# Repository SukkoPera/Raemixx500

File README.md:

# Rämixx500
Rämixx500 is an Open Hardware remake of the Commodore Amiga 500+ mainboard, revision 8A.1.

## Summary
Many Amiga 500+ computers are suffering an early death because of the built-in barrel battery that powers their internal real-time clocks. Such batteries have long exceeded their planned lives and in many cases have started to leak alkaline liquids over the mainboard, corroding copper traces and destroying components.

This damage can sometimes be repaired trivially, but many times it requires a lot of time and effort. Sometimes it adds up to other damage occurred over time and so it would just be better to have a new board built with new components to move the few critical chips over. Amiga mainboards haven't been produced for the last 30 years, but they are relatively simple by today's standards, thus an amateur project to make new ones was started.

There are other projects with the same goal out there, but none of them is Open Source and none of them comes with both schematics and board. This is a big advantage, since anyone can modify the board and make new improved versions, as long as they release their modifications it with the same license. I have come up with [some ideas for improvements](https://github.com/SukkoPera/Raemixx500/issues/14), feel free to help :).

The first version of the board was released in April 2020 as untested, in the hope that someone from the Amiga "Community" would jump in and help with the testing. Well, that took quite some time but in the end someone finally understood that Open Hardware is about trying to do your part rather than coming up with [heaps of useless talking and moaning](https://news.ycombinator.com/item?id=22887349) or [blatant stealing](https://retrotechlyfe.com/home/ols/products/commodore-amiga-500-computer-motherboard-logic-board-premium-gold-immersed-traces-stellar-signal-integrity) and allowed this project to reach the next milestone. So despite knowing he could be jumping into the void, fellow Italian living in Japan Edoardo Auteri put confidence, money, time and effort into assembling a board and testing it thoroughly. While he was at it, he came up with some interesting ideas which ultimately encouraged me to make Version 2, which **fully passed all tests**. You can read more about the development and testing of the board on [the official development blog](https://hackaday.io/project/180442-rmixx500-amiga-500-mainboard).

## Differences from Original
The initial objective was to come up with a new mainboard as similar to the original one as possible, while including minor modifications that would improve its usability. This mainboard was designed with *reasonable* - not *maniacal* - accuracy to the original design. Most care was taken in the positioning of components that ought to be in a certain position (i.e.: screw holes and I/O connectors), to ensure drop-in replaceability. Other components and tracks are "more or less" there, but as the board was wholly laid out from scratch by hand, don't expect sub-millimeter accuracy.

Some modifications were soon added in, in the hope that they would be useful. Let's make it clear straight from the beginning that **most of these improvements and modifications are completely optional and actually disabled by default**. This means that you can just ignore them and everything will work as it did on the original A500+ board. If you want to take advantage of them instead, you will need to do some work.

### Modifications introduced in V2
* **Buffered Video Synchronization Signals**: This will make the VSYNC and HSYNC signals going out from the DB23 connector somewhat "stronger", which should improve video quality and also allow using fully passive (i.e.: just wires) RGB to VGA cables (but please note that the signal will still be 15 kHz so a scandoubler will still be required with most VGA monitors). To enable this, cut both the JP99H/V jumpers, solder a 74HCT14 SOIC chip at U94 (yes, it's surface-mount, but the available space was limited) and a 100-330nF ceramic capacitor at C94. Note that if you want to get back to unbuffered (why???) you will **both** need to unsolder U94 and close the jumpers again, otherwise you will definitely damage your Denise and/or buffer. One small caveat: you'd better decide what to do with this mod before you solder the nearby components, as space around U94 is really tight and (un)soldering it with the other components in place is not a task for the faint-hearted.

* **ESD Protection for the Joystick Ports**: While connecting controllers blindly is **still not recommended**, you can add some diodes that *should* hopefully avoid damage to the internal chips whenever you do so. These won't hurt in any case, so why not? Just solder some AT1042 chips at U90-U93. Yes, they are small but you can make it.

* **Hard Disk LED**: If you use an internal expansion board that provides an IDE connector, you will feel the need for a LED flashing whenever the disk is accessed. If you connect a wire from pin 39 of your CF adapter to the new *HDACT* connector right in the middle of the board, the *Floppy* light will also flash when the hard disk is accessed. To get this to work, solder a 2n3906 transistor at Q99 and resistors R98 (10k) and R99 (4.7k).

* **Alternative Footprint for the Line Filter**: The original line filter (LF1) was probably a custom part, but in any case it's impossible to find these days. Luckily a functionally-equivalent part is available (Laird Z131B-10) but it has a different footprint, so the latter was added at LF99. Be **very careful** when soldering this, as it is very easy to make a solder bridge between the pads of LF1 and those of LF99 and short out the power rails.

* **Alternative SMD Footprints for the JFETs**: Q321/331 are a bit hard to find these days in the TO-92 package, so alternative surface-mount SOT-23 footprints were added (Q921/931). Choose the package you prefer and only solder one of each.

* **More Accurate Dimensions**: While V1 was already pretty close to the original board, the new version should be right on the money. Placement of the audio and mouse ports was also improved.

* **More Detailed Silkscreen**: The values of all resistors, capacitors and chips are now printed on the silkscreen, which makes the assembly process quicker and less error-prone.

* **Improved Routing and Ground Plane**: Some tracks were slightly altered in the hope of achieving improved signal integrity. Lower impedance to ground also resulted in all chips running a few degrees Celsius colder.

* One more change lies in the license: **the project is now released under CC BY-NC-SA**, which is not too different in practice from the license we were using before, except that **any commercial use is now prohibited**. I know this makes the project non-free, strictly speaking. While I am sorry for that, that's what the behaviour of the "community" has led me to. Blame them, not me.

### Modifications Introduced in V1/V1B
* **Support for VBB Agnus**: This board is compatible with a few different Fat Agnus models, namely: 318069-10 and 390544-03 for PAL or -11 and -02 for NTSC (FIXME). The 390544 models have a *VBB* marking and require a 100-330nF cap to be fitted at C99, which must instead be left unpopulated for the other models. Note that while all the mentioned models are also numbered *8375*, **not all 8375 models are actually compatible**: please check that the extended part number is one of those mentioned above (these usually came from "wide label" A500 featuring a Rev.8A mainboard, A500+ or A600 computers, if you got your Agnus somewhere else, it likely isn't the correct one). 8372 and 8371 models are definitely not compatible either at the moment. And before you ask: no, Alice chips will never work.

* **Mono Audio Link**: This feature was lifted from the A600/A1200 and will transparently downmix the audio output to mono whenever you only plug one of the two audio connectors (any of the two), while on the original A500 you would only hear the corresponding channel. Whenever you plug both connectors, the channels will separate automatically. This is the reason why this feature is enabled by default, in that it is completely transparent to the user in normal conditions.

* **Alternative Power Connector**: Besides using the original A500 power connector, which can be expensive to get hold of, you can use common and cheap DIN-6 or DIN-8 connectors. Have a look [at the wiki](https://github.com/SukkoPera/Raemixx500/wiki/Power-Connector-Wiring) for more information, including a wiring method.

* **Kickstart Switcher**: This is a set of jumpers that will allow you to store more than one Kickstart image on a single ROM chip and enable one at will. If you want to use it, have a look [at the wiki](https://github.com/SukkoPera/Raemixx500/wiki/Kickstart-Switcher).

* **Drive Switcher**: This is a pretty basic drive switcher which will result in the first external drive to be seen as DF0: and the actual DF0: to become invisible. Instructions for how to use it are on [the wiki](https://github.com/SukkoPera/Raemixx500/wiki/Drive-Switcher) as usual.

### Other Minor Things Worth Mentioning
Following is a list of deliberate changes with respect to the original layout of the A500+ rev.8A.1 board:
- The footprints for all DIP chips use "long pads". This makes them easier to solder and more solid to the board should you need to rework them. This forced a few tracks running very close to the original pads to be slightly offset away.
- The power connector footprint was altered to either accept the original connector, a DIN-6 or a DIN-8. I actually recommend the latter, as it uses more than one pin for the +5V and +12V rails, allowing for more current.
- The floppy connector footprint was changed to that of a full IDC connector.
- The barrel battery was replaced with a BS-7 battery holder for a normal (non-rechargeable) CR2032 battery. Consequently, R913 has been replaced with a diode (labeled D913) and a couple of tracks needed some displacement.
- The need to solder D912 to a leg of the former R913 has been removed. Just solder it in its place.
- The RCA jacks for the audio and composite video outputs have been replaced with some that can actually be found nowadays (i.e.: those that were used on A600/A1200). This resulted in having to relocate R409 (whose original position seemed somehow improvised anyway...).
- The silkscreen for some components does not match the original one. I used the built-in KiCad footprints as-is, when available.
- The silkscreen and pitch of C303, C304 and C306 have been made smaller so that they don't overlap.
- Speaking about the silkscreen, I have been quite liberal with it. I have used the default KiCad font and I did not follow the original label placement at all costs. I did this since today's technology can give us a bit more resolution in silkscreen printing, and I think that is worth using for the sake of clarity. Some ground stitching vias were slightly offset to make up space for labels.
- The vias inside the pads of JP10A and JP11 have been slightly offset so that they are outside the pads.
- The ground fill is autogenerated by KiCad, so it won't match the original exactly.
- Probably there's something more I've forgotten.

## Assembly and Installation
Please refer to [the wiki](https://github.com/SukkoPera/Raemixx500/wiki).

## Releases
If you want to get this board produced, you are recommended to get [the latest release](https://github.com/SukkoPera/Raemixx500/releases) rather than the current git version, as the latter might be under development and is not guaranteed to be working.

Every release is accompanied by its Bill Of Materials (BOM) file and any relevant notes about it, which you are recommended to read carefully.

**I am not providing ready-to-use gerber files**. If all you want is **to get boards made, I would really appreciate if you did so [in a way that supports the project](#support-the-project)**.

## License
The Rämixx500 documentation, including the design itself, is copyright &copy; SukkoPera 2019-2021 and is licensed under the [Creative Commons Attribution-NonCommercial-ShareAlike 4.0 International License](https://creativecommons.org/licenses/by-nc-sa/4.0/).

This documentation is distributed *as is* and WITHOUT ANY EXPRESS OR IMPLIED WARRANTIES whatsoever with respect to its functionality, operability or use, including, without limitation, any implied warranties OF MERCHANTABILITY, SATISFACTORY QUALITY, FITNESS FOR A PARTICULAR PURPOSE or infringement. We expressly disclaim any liability whatsoever for any direct, indirect, consequential, incidental or special damages, including, without limitation, lost revenues, lost profits, losses resulting from business interruption or loss of data, regardless of the form of action or legal theory under which the liability may be asserted, even if advised of the possibility or likelihood of such damages.

This said, I would like this project to progress further. **If anyone would like to do major work on it but is discouraged to do so by the impossibility to exploit the work commercially, please get in touch with me**, I will grant you a private license which will allow you to do that.

## Support the Project
There are currently no "official" sellers selling this board. If someone wants to become "official", just get in touch with me, conditions are very simple (i.e.: we agree on a price cap and you donate a fraction of your earnings to some charity of your choice, that's it).

This means that all the boards currently on sale on eBay or anywhere else are breaching the licensing terms, so you are strongly recommended not to buy from these sellers and maybe you should even report them to eBay, since they are not paying attention to me (neither the sellers themselves, nor eBay...).

The recommended way to get a board is to have some produced by PCBWay through this link:

You get my gratitude and cheap, professionally-made and good quality PCBs, I get some credit that will help with this and [other projects](https://www.pcbway.com/project/member/shareproject/?bmbid=41100). You won't even have to worry about the various PCB options, it's all pre-configured for you!

Also, if you still have to register, [you can use this link](https://www.pcbway.com/setinvite.aspx?inviteid=41100) to get some bonus initial credit (and yield me some more).

You will have to order at least 5 PCBs, but then you can share the extras with your friends or put them up for sale on forums or anywhere **at cost**.

If you think PCBWay is too expensive, just generate the Gerber files in KiCad (it takes 5 seconds, maybe 30 if you've never done it before) and order from your favourite supplier.

## Thanks
- Commodore, for making the coolest machine ever.
- [Edoardo Auteri](https://github.com/kinmami) for putting confidence in me and joining the project. He is also the person that you should be thankful to if this project is still open-source.
- [Amiga PCB Explorer](http://amigapcb.org), a fundamental tool to follow the original track placement.
- [amigawiki](https://www.amigawiki.org/doku.php?id=en:service:schematics), mainly for the schematics but also for the whole lot of information they provide.
- majinga for helping with the measuring.
- [Walter](http://smisioto.no-ip.org/elettronica/kicad/kicad-en.htm) for some of the footprints/3D models used.
- [DiagROM](http://www.diagrom.com/) for inspiring the selling clause.
- [Jason Warnes](https://www.everythingamiga.com/2019/10/alternative-to-amiga-500-600-1200-power-connector.html) for information about the original power connector and how to replace it with a DIN-8.
- [Szabó Zoltán](https://twitter.com/DeGenTd) for designing the board logo.
- [Workshopshed](https://twitter.com/Workshopshed) for the 3D models of the EMI filters.
- [StormTrooper](https://github.com/StormTrooper/Commodore-Plus4) for a few other 3D models, taken from his Plus/4 remake.

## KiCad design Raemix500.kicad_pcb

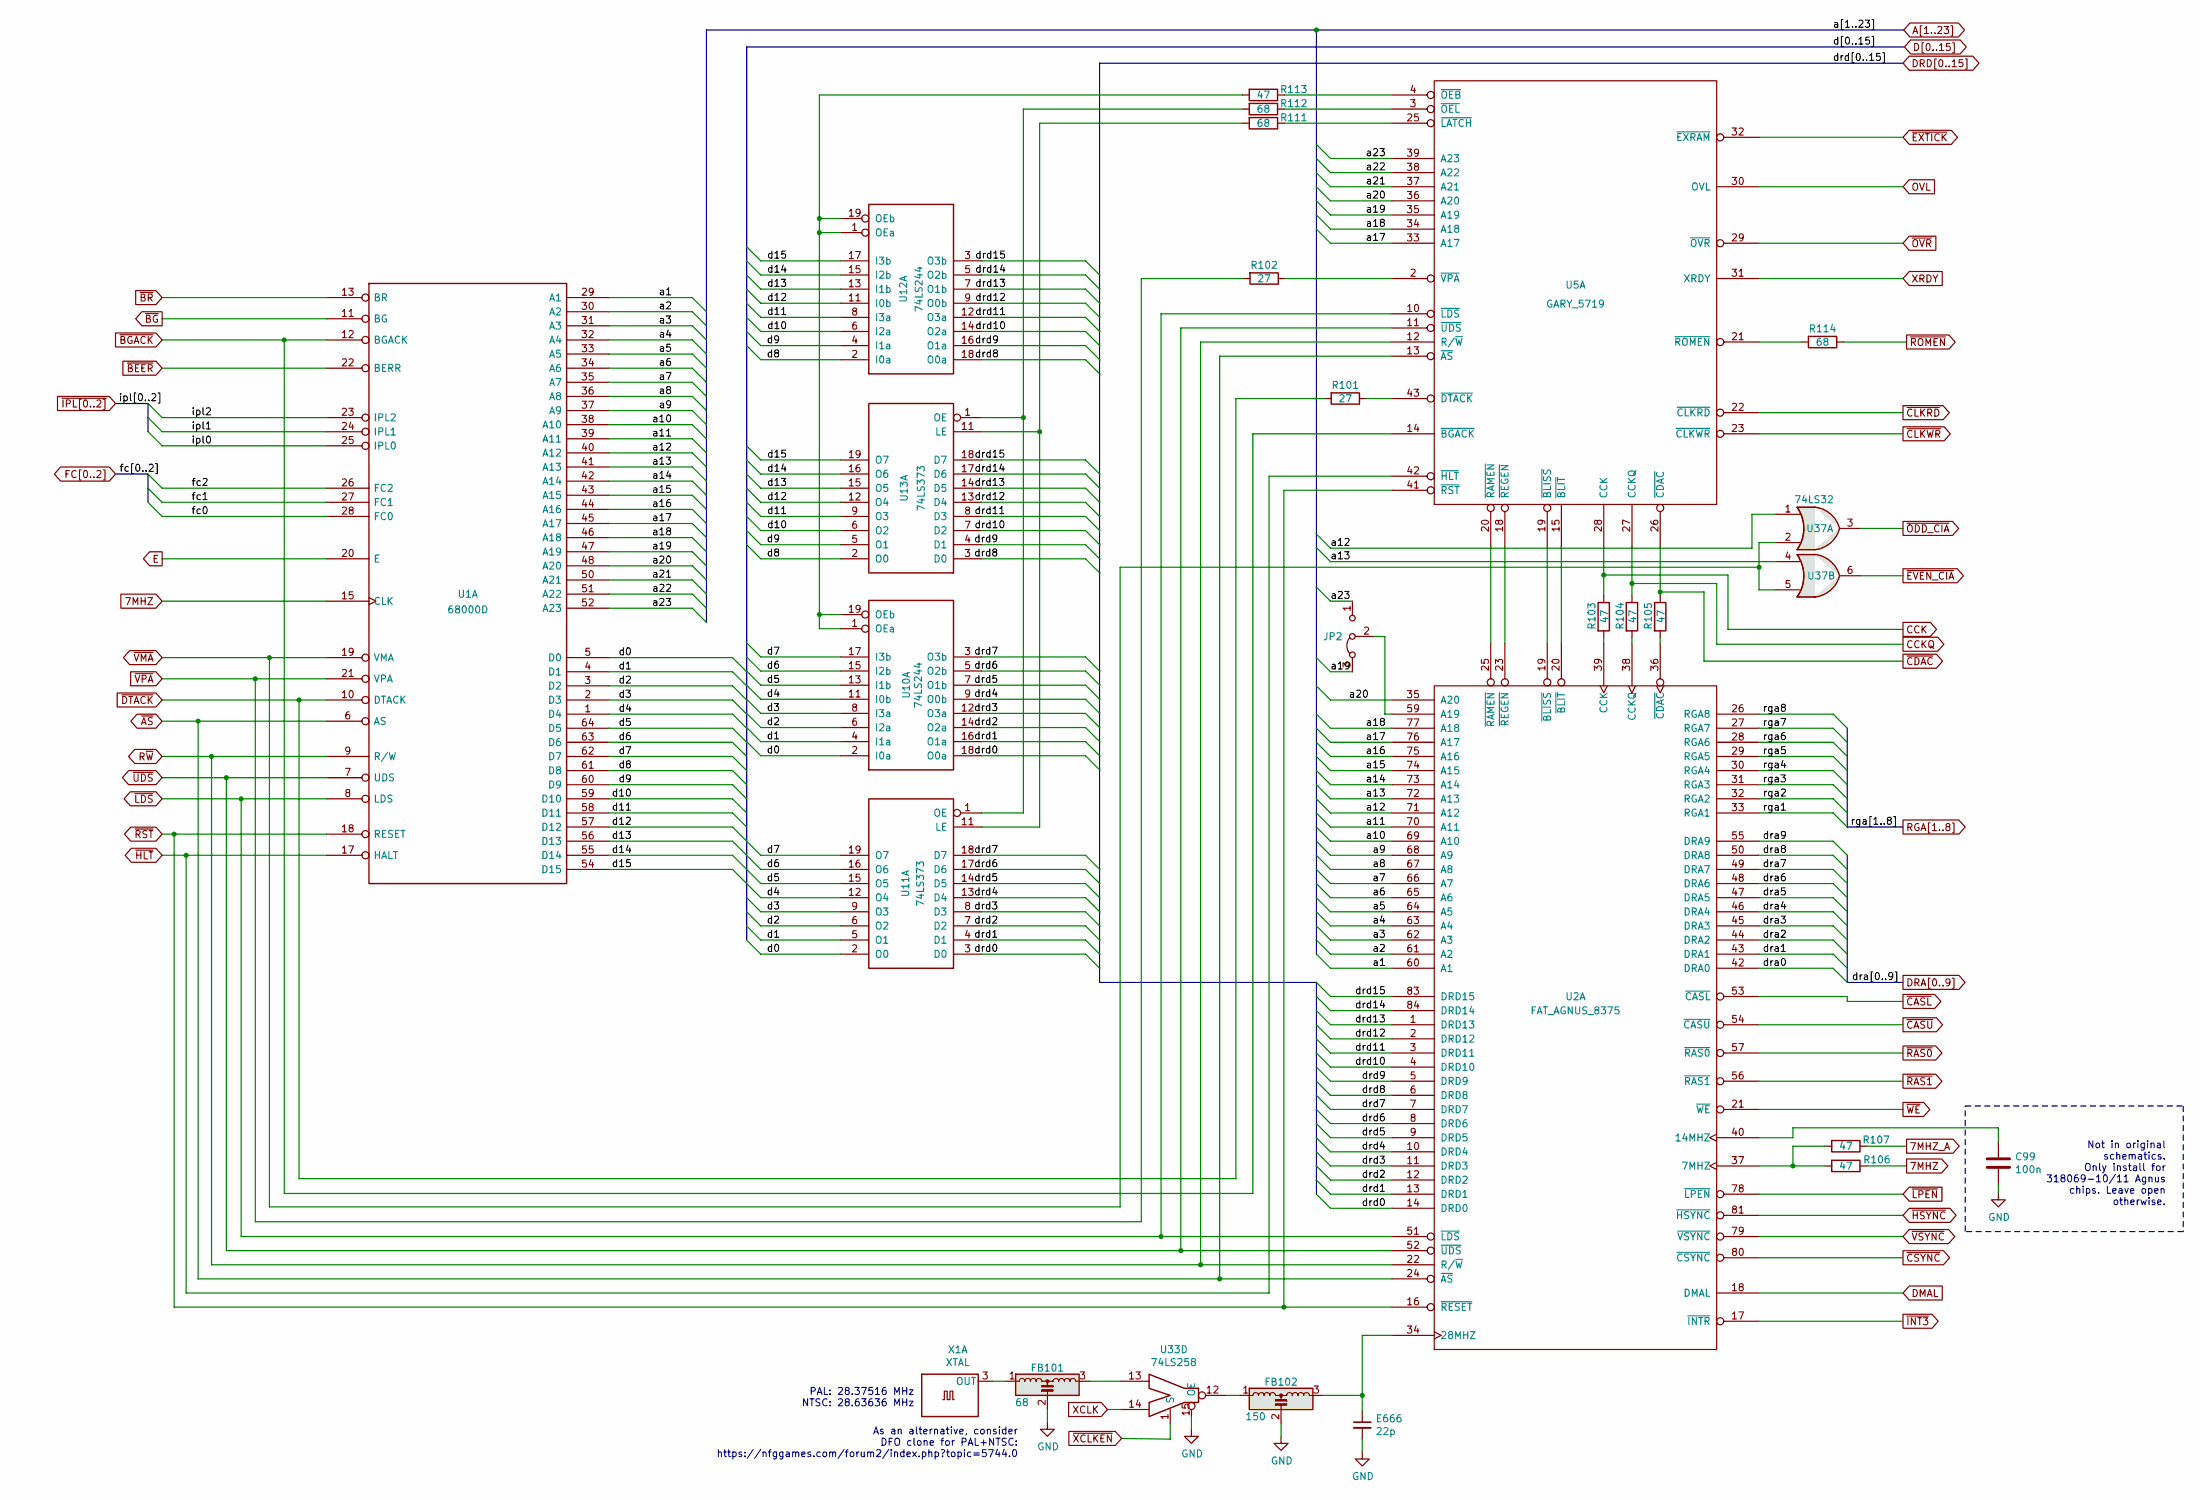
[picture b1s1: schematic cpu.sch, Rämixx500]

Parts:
C99: 100n
E666: 22p; C_Axial_L6.3mm_D2.5mm_P10.16mm
FB101: 68; EMI_Filter_Long
FB102: 150; EMI_Filter_Long
JP2: Jumper_3_Bridged23; Jumper3-Bridged23
R101, R102: 27; R_Axial_DIN0309_L9.0mm_D3.2mm_P12.70mm_Horizontal
R103, R104, R105, R106, R107, R113: 47; R_Axial_DIN0309_L9.0mm_D3.2mm_P12.70mm_Horizontal
R111, R112, R114: 68; R_Axial_DIN0309_L9.0mm_D3.2mm_P12.70mm_Horizontal
U1: 68000D; DIP-64_W22.86mm_Socket_LongPads
U2: FAT_AGNUS_8375; PLCC-84_THT-Socket
U5: GARY_5719; DIP-48_W15.24mm_Socket_LongPads
U10, U12: 74LS244; DIP-20_W7.62mm_Socket_LongPads
U11, U13: 74LS373; DIP-20_W7.62mm_Socket_LongPads
U33: 74LS258; DIP-16_W7.62mm_Socket_LongPads
U37: 74LS32; DIP-14_W7.62mm_Socket_LongPads
X1: XTAL; Xtal

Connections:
7MHZ: R106.1, U1.15 (CLK); also elsewhere on the board
7MHZ_A: R107.1; also elsewhere on the board
A1: U1.29 (A1), U2.60 (A1); also elsewhere on the board
A2: U1.30 (A2), U2.61 (A2); also elsewhere on the board
A3: U1.31 (A3), U2.62 (A3); also elsewhere on the board
A4: U1.32 (A4), U2.63 (A4); also elsewhere on the board
A5: U1.33 (A5), U2.64 (A5); also elsewhere on the board
A6: U1.34 (A6), U2.65 (A6); also elsewhere on the board
A7: U1.35 (A7), U2.66 (A7); also elsewhere on the board
A8: U1.36 (A8), U2.67 (A8); also elsewhere on the board
A9: U1.37 (A9), U2.68 (A9); also elsewhere on the board
A10: U1.38 (A10), U2.69 (A10); also elsewhere on the board
A11: U1.39 (A11), U2.70 (A11); also elsewhere on the board
A12: U1.40 (A12), U2.71 (A12), U37.1; also elsewhere on the board
A13: U1.41 (A13), U2.72 (A13), U37.4; also elsewhere on the board
A14: U1.42 (A14), U2.73 (A14); also elsewhere on the board
A15: U1.43 (A15), U2.74 (A15); also elsewhere on the board
A16: U1.44 (A16), U2.75 (A16); also elsewhere on the board
A17: U1.45 (A17), U2.76 (A17), U5.33 (A17); also elsewhere on the board
A18: U1.46 (A18), U2.77 (A18), U5.34 (A18); also elsewhere on the board
A19: JP2.3 (B), U1.47 (A19), U5.35 (A19); also elsewhere on the board
A20: U1.48 (A20), U2.35 (A20), U5.36 (A20); also elsewhere on the board
A21: U1.50 (A21), U5.37 (A21); also elsewhere on the board
A22: U1.51 (A22), U5.38 (A22); also elsewhere on the board
A23: JP2.1 (A), U1.52 (A23), U5.39 (A23); also elsewhere on the board
CCK: R103.1, U5.28 (CCK); also elsewhere on the board
CCKQ: R104.1, U5.27 (CCKQ); also elsewhere on the board
D0: U1.5 (D0), U10.2 (I0a), U11.2 (O0); also elsewhere on the board
D1: U1.4 (D1), U10.4 (I1a), U11.5 (O1); also elsewhere on the board
D2: U1.3 (D2), U10.6 (I2a), U11.6 (O2); also elsewhere on the board
D3: U1.2 (D3), U10.8 (I3a), U11.9 (O3); also elsewhere on the board
D4: U1.1 (D4), U10.11 (I0b), U11.12 (O4); also elsewhere on the board
D5: U1.64 (D5), U10.13 (I1b), U11.15 (O5); also elsewhere on the board
D6: U1.63 (D6), U10.15 (I2b), U11.16 (O6); also elsewhere on the board
D7: U1.62 (D7), U10.17 (I3b), U11.19 (O7); also elsewhere on the board
D8: U1.61 (D8), U12.2 (I0a), U13.2 (O0); also elsewhere on the board
D9: U1.60 (D9), U12.4 (I1a), U13.5 (O1); also elsewhere on the board
D10: U1.59 (D10), U12.6 (I2a), U13.6 (O2); also elsewhere on the board
D11: U1.58 (D11), U12.8 (I3a), U13.9 (O3); also elsewhere on the board
D12: U1.57 (D12), U12.11 (I0b), U13.12 (O4); also elsewhere on the board
D13: U1.56 (D13), U12.13 (I1b), U13.15 (O5); also elsewhere on the board
D14: U1.55 (D14), U12.15 (I2b), U13.16 (O6); also elsewhere on the board
D15: U1.54 (D15), U12.17 (I3b), U13.19 (O7); also elsewhere on the board
DMAL: U2.18 (DMAL); also elsewhere on the board
DRA0: U2.42 (DRA0); also elsewhere on the board
DRA1: U2.43 (DRA1); also elsewhere on the board
DRA2: U2.44 (DRA2); also elsewhere on the board
DRA3: U2.45 (DRA3); also elsewhere on the board
DRA4: U2.46 (DRA4); also elsewhere on the board
DRA5: U2.47 (DRA5); also elsewhere on the board
DRA6: U2.48 (DRA6); also elsewhere on the board
DRA7: U2.49 (DRA7); also elsewhere on the board
DRA8: U2.50 (DRA8); also elsewhere on the board
DRA9: U2.55 (DRA9); also elsewhere on the board
DRD0: U2.14 (DRD0), U10.18 (O0a), U11.3 (D0); also elsewhere on the board
DRD1: U2.13 (DRD1), U10.16 (O1a), U11.4 (D1); also elsewhere on the board
DRD2: U2.12 (DRD2), U10.14 (O2a), U11.7 (D2); also elsewhere on the board
DRD3: U2.11 (DRD3), U10.12 (O3a), U11.8 (D3); also elsewhere on the board
DRD4: U2.10 (DRD4), U10.9 (O0b), U11.13 (D4); also elsewhere on the board
DRD5: U2.9 (DRD5), U10.7 (O1b), U11.14 (D5); also elsewhere on the board
DRD6: U2.8 (DRD6), U10.5 (O2b), U11.17 (D6); also elsewhere on the board
DRD7: U2.7 (DRD7), U10.3 (O3b), U11.18 (D7); also elsewhere on the board
DRD8: U2.6 (DRD8), U12.18 (O0a), U13.3 (D0); also elsewhere on the board
DRD9: U2.5 (DRD9), U12.16 (O1a), U13.4 (D1); also elsewhere on the board
DRD10: U2.4 (DRD10), U12.14 (O2a), U13.7 (D2); also elsewhere on the board
DRD11: U2.3 (DRD11), U12.12 (O3a), U13.8 (D3); also elsewhere on the board
DRD12: U2.2 (DRD12), U12.9 (O0b), U13.13 (D4); also elsewhere on the board
DRD13: U2.1 (DRD13), U12.7 (O1b), U13.14 (D5); also elsewhere on the board
DRD14: U2.84 (DRD14), U12.5 (O2b), U13.17 (D6); also elsewhere on the board
DRD15: U2.83 (DRD15), U12.3 (O3b), U13.18 (D7); also elsewhere on the board
E: U1.20 (E); also elsewhere on the board
FC0: U1.28 (FC0); also elsewhere on the board
FC1: U1.27 (FC1); also elsewhere on the board
FC2: U1.26 (FC2); also elsewhere on the board
GND: C99.2, E666.2, FB101.2, FB102.2, U33.15 (OE); also elsewhere on the board
unnamed: C99.1, U2.40 (14MHZ)
unnamed: E666.1, FB102.3, U2.34 (28MHZ)
unnamed: FB101.1, X1.3 (OUT)
unnamed: FB101.3, U33.13
unnamed: FB102.1, U33.12
unnamed: JP2.2 (C), U2.59 (A19)
unnamed: R101.1, U5.43 (~DTACK)
unnamed: R102.1, U5.2 (~VPA)
unnamed: R103.2, U2.39 (CCK)
unnamed: R104.2, U2.38 (CCKQ)
unnamed: R105.2, U2.36 (~CDAC)
unnamed: R106.2, R107.2, U2.37 (7MHZ)
unnamed: R111.1, U5.25 (~LATCH)
unnamed: R111.2, U11.11 (LE), U13.11 (LE)
unnamed: R112.1, U5.3 (~OEL)
unnamed: R112.2, U11.1 (OE), U13.1 (OE)
unnamed: R113.1, U5.4 (~OEB)
unnamed: R113.2, U10.1 (OEa), U10.19 (OEb), U12.1 (OEa), U12.19 (OEb)
unnamed: R114.2, U5.21 (~ROMEN)
unnamed: U2.19 (~BLISS), U5.19 (~BLISS)
unnamed: U2.20 (~BLIT), U5.15 (~BLIT)
unnamed: U2.23 (~REGEN), U5.18 (~REGEN)
unnamed: U2.25 (~RAMEN), U5.20 (~RAMEN)
OVL: U5.30 (OVL); also elsewhere on the board
RGA1: U2.33 (RGA1); also elsewhere on the board
RGA2: U2.32 (RGA2); also elsewhere on the board
RGA3: U2.31 (RGA3); also elsewhere on the board
RGA4: U2.30 (RGA4); also elsewhere on the board
RGA5: U2.29 (RGA5); also elsewhere on the board
RGA6: U2.28 (RGA6); also elsewhere on the board
RGA7: U2.27 (RGA7); also elsewhere on the board
RGA8: U2.26 (RGA8); also elsewhere on the board
R~W: U1.9 (R/W), U2.22 (R/~W), U5.12 (R/~W); also elsewhere on the board
XCLK: U33.14; also elsewhere on the board
XRDY: U5.31 (XRDY); also elsewhere on the board
~AS: U1.6 (AS), U2.24 (~AS), U5.13 (~AS); also elsewhere on the board
~BEER: U1.22 (BERR); also elsewhere on the board
~BG: U1.11 (BG); also elsewhere on the board
~BGACK: U1.12 (BGACK), U5.14 (~BGACK); also elsewhere on the board
~BR: U1.13 (BR); also elsewhere on the board
~CASL: U2.53 (~CASL); also elsewhere on the board
~CASU: U2.54 (~CASU); also elsewhere on the board
~CDAC: R105.1, U5.26 (~CDAC); also elsewhere on the board
~CLKRD: U5.22 (~CLKRD); also elsewhere on the board
~CLKWR: U5.23 (~CLKWR); also elsewhere on the board
~CSYNC: U2.80 (~CSYNC); also elsewhere on the board
~DTACK: R101.2, U1.10 (DTACK); also elsewhere on the board
~EVEN_CIA: U37.6; also elsewhere on the board
~EXTICK: U5.32 (~EXRAM); also elsewhere on the board
~HLT: U1.17 (HALT), U5.42 (~HLT); also elsewhere on the board
~HSYNC: U2.81 (~HSYNC); also elsewhere on the board
~INT3: U2.17 (~INTR); also elsewhere on the board
~IPL0: U1.25 (IPL0); also elsewhere on the board
~IPL1: U1.24 (IPL1); also elsewhere on the board
~IPL2: U1.23 (IPL2); also elsewhere on the board
~LDS: U1.8 (LDS), U2.51 (~LDS), U5.10 (~LDS); also elsewhere on the board
~LPEN: U2.78 (~LPEN); also elsewhere on the board
~ODD_CIA: U37.3; also elsewhere on the board
~OVR: U5.29 (~OVR); also elsewhere on the board
~RAS0: U2.57 (~RAS0); also elsewhere on the board
~RAS1: U2.56 (~RAS1); also elsewhere on the board
~ROMEN: R114.1; also elsewhere on the board
~RST: U1.18 (RESET), U2.16 (~RESET), U5.41 (~RST); also elsewhere on the board
~UDS: U1.7 (UDS), U2.52 (~UDS), U5.11 (~UDS); also elsewhere on the board
~VMA: U1.19 (VMA), U37.2, U37.5; also elsewhere on the board
~VPA: R102.2, U1.21 (VPA); also elsewhere on the board
~VSYNC: U2.79 (~VSYNC); also elsewhere on the board
~WE: U2.21 (~WE); also elsewhere on the board

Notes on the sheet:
Not in original schematics. Only install for 318069-10/11 Agnus chips. Leave open otherwise.
As an alternative, consider DFO clone for PAL+NTSC: https://nfggames.com/forum2/index.php?topic=5744.0
PAL: 28.37516 MHz NTSC: 28.63636 MHz

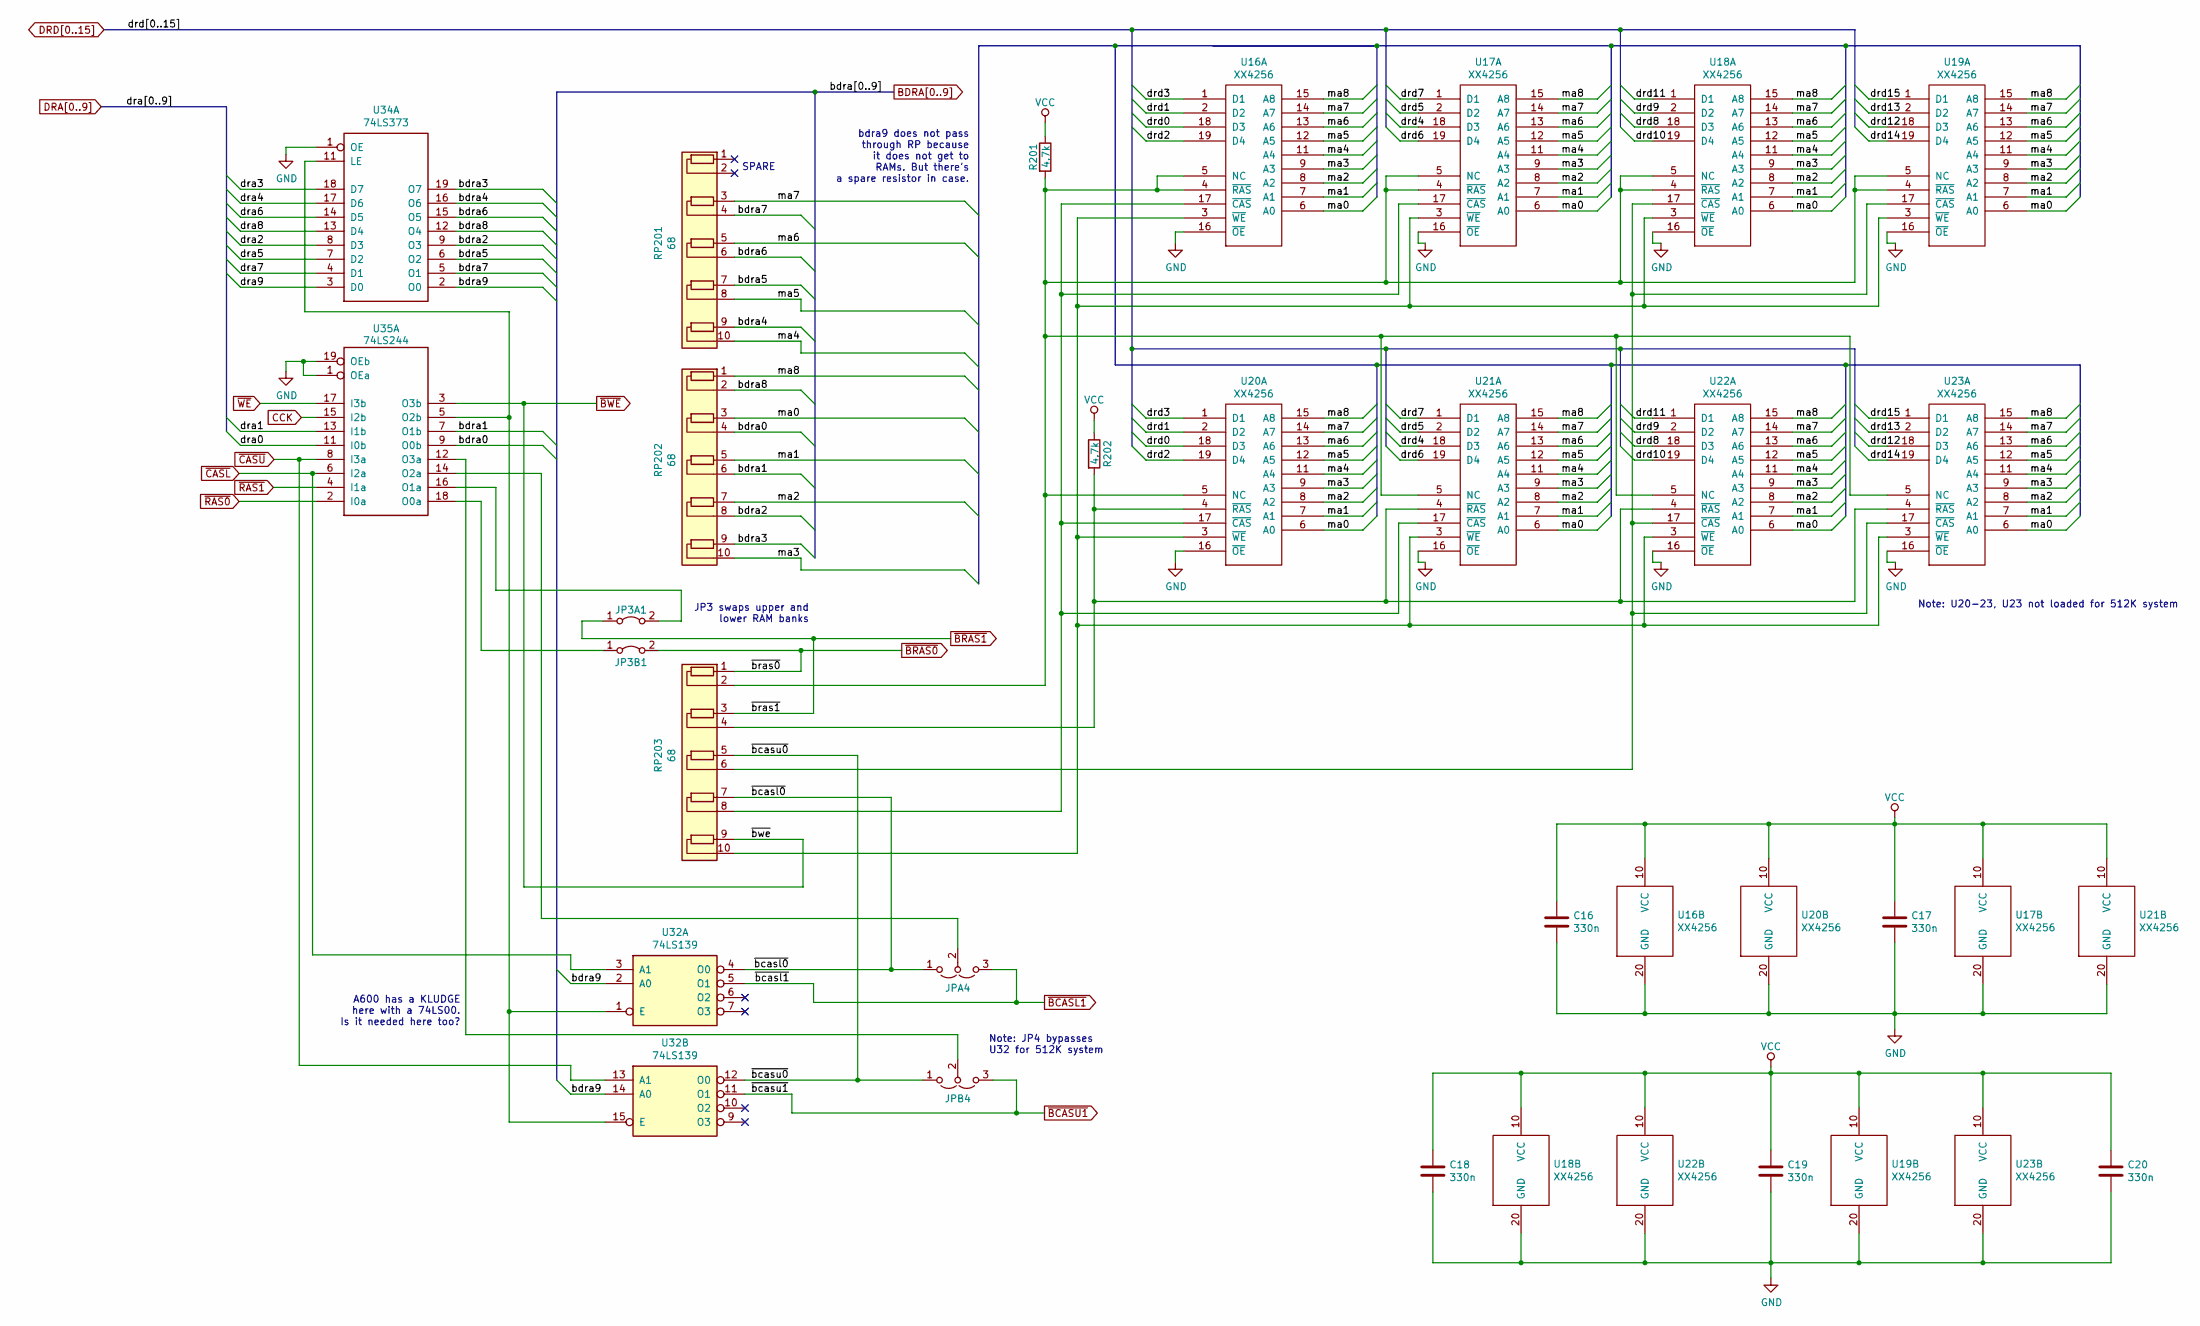
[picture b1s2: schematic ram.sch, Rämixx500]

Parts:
C16, C17, C18, C19, C20: 330n; C_Axial_L6.3mm_D2.5mm_P10.16mm
JP3A1, JP3B1: Jumper_2_Bridged; Jumper2-Bridged
JPA4: Jumper_3_Open; Jumper3-Open
JPB4: Jumper_3_Open; Jumper3-Open
R201, R202: 4.7k; R_Axial_DIN0309_L9.0mm_D3.2mm_P12.70mm_Horizontal
RP201, RP202, RP203: 68; R_Array_SIP10
U16, U17, U18, U19, U20, U21, U22, U23: XX4256; DIP-20_W7.62mm_Socket_LongPads
U32: 74LS139; DIP-16_W7.62mm_Socket_LongPads
U34: 74LS373; DIP-20_W7.62mm_Socket_LongPads
U35: 74LS244; DIP-20_W7.62mm_Socket_LongPads

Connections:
/RAM/ma0: RP202.3 (R2.1), U16.6 (A0), U17.6 (A0), U18.6 (A0), U19.6 (A0), U20.6 (A0), U21.6 (A0), U22.6 (A0), U23.6 (A0)
/RAM/ma1: RP202.5 (R3.1), U16.7 (A1), U17.7 (A1), U18.7 (A1), U19.7 (A1), U20.7 (A1), U21.7 (A1), U22.7 (A1), U23.7 (A1)
/RAM/ma2: RP202.7 (R4.1), U16.8 (A2), U17.8 (A2), U18.8 (A2), U19.8 (A2), U20.8 (A2), U21.8 (A2), U22.8 (A2), U23.8 (A2)
/RAM/ma3: RP202.10 (R5.2), U16.9 (A3), U17.9 (A3), U18.9 (A3), U19.9 (A3), U20.9 (A3), U21.9 (A3), U22.9 (A3), U23.9 (A3)
/RAM/ma4: RP201.10 (R5.2), U16.11 (A4), U17.11 (A4), U18.11 (A4), U19.11 (A4), U20.11 (A4), U21.11 (A4), U22.11 (A4), U23.11 (A4)
/RAM/ma5: RP201.8 (R4.2), U16.12 (A5), U17.12 (A5), U18.12 (A5), U19.12 (A5), U20.12 (A5), U21.12 (A5), U22.12 (A5), U23.12 (A5)
/RAM/ma6: RP201.5 (R3.1), U16.13 (A6), U17.13 (A6), U18.13 (A6), U19.13 (A6), U20.13 (A6), U21.13 (A6), U22.13 (A6), U23.13 (A6)
/RAM/ma7: RP201.3 (R2.1), U16.14 (A7), U17.14 (A7), U18.14 (A7), U19.14 (A7), U20.14 (A7), U21.14 (A7), U22.14 (A7), U23.14 (A7)
/RAM/ma8: RP202.1 (R1.1), U16.15 (A8), U17.15 (A8), U18.15 (A8), U19.15 (A8), U20.15 (A8), U21.15 (A8), U22.15 (A8), U23.15 (A8)
/RAM/~bcasl0: JPA4.1 (A), RP203.7 (R4.1), U32.4 (O0)
/RAM/~bcasu0: JPB4.1 (A), RP203.5 (R3.1), U32.12 (O0)
BDRA0: RP202.4 (R2.2), U35.9 (O0b); also elsewhere on the board
BDRA1: RP202.6 (R3.2), U35.7 (O1b); also elsewhere on the board
BDRA2: RP202.8 (R4.2), U34.9 (O3); also elsewhere on the board
BDRA3: RP202.9 (R5.1), U34.19 (O7); also elsewhere on the board
BDRA4: RP201.9 (R5.1), U34.16 (O6); also elsewhere on the board
BDRA5: RP201.7 (R4.1), U34.6 (O2); also elsewhere on the board
BDRA6: RP201.6 (R3.2), U34.15 (O5); also elsewhere on the board
BDRA7: RP201.4 (R2.2), U34.5 (O1); also elsewhere on the board
BDRA8: RP202.2 (R1.2), U34.12 (O4); also elsewhere on the board
BDRA9: U32.2 (A0), U32.14 (A0), U34.2 (O0)
CCK: U35.15 (I2b); also elsewhere on the board
DRA0: U35.11 (I0b); also elsewhere on the board
DRA1: U35.13 (I1b); also elsewhere on the board
DRA2: U34.8 (D3); also elsewhere on the board
DRA3: U34.18 (D7); also elsewhere on the board
DRA4: U34.17 (D6); also elsewhere on the board
DRA5: U34.7 (D2); also elsewhere on the board
DRA6: U34.14 (D5); also elsewhere on the board
DRA7: U34.4 (D1); also elsewhere on the board
DRA8: U34.13 (D4); also elsewhere on the board
DRA9: U34.3 (D0); also elsewhere on the board
DRD0: U16.18 (D3), U20.18 (D3); also elsewhere on the board
DRD1: U16.2 (D2), U20.2 (D2); also elsewhere on the board
DRD2: U16.19 (D4), U20.19 (D4); also elsewhere on the board
DRD3: U16.1 (D1), U20.1 (D1); also elsewhere on the board
DRD4: U17.18 (D3), U21.18 (D3); also elsewhere on the board
DRD5: U17.2 (D2), U21.2 (D2); also elsewhere on the board
DRD6: U17.19 (D4), U21.19 (D4); also elsewhere on the board
DRD7: U17.1 (D1), U21.1 (D1); also elsewhere on the board
DRD8: U18.18 (D3), U22.18 (D3); also elsewhere on the board
DRD9: U18.2 (D2), U22.2 (D2); also elsewhere on the board
DRD10: U18.19 (D4), U22.19 (D4); also elsewhere on the board
DRD11: U18.1 (D1), U22.1 (D1); also elsewhere on the board
DRD12: U19.18 (D3), U23.18 (D3); also elsewhere on the board
DRD13: U19.2 (D2), U23.2 (D2); also elsewhere on the board
DRD14: U19.19 (D4), U23.19 (D4); also elsewhere on the board
DRD15: U19.1 (D1), U23.1 (D1); also elsewhere on the board
GND: C16.2, C17.2, C18.2, C19.2, C20.2, U16.16 (~OE), U16.20 (GND), U17.16 (~OE), U17.20 (GND), U18.16 (~OE), U18.20 (GND), U19.16 (~OE), U19.20 (GND), U20.16 (~OE), U20.20 (GND), U21.16 (~OE), U21.20 (GND), U22.16 (~OE), U22.20 (GND), U23.16 (~OE), U23.20 (GND), U34.1 (OE), U35.1 (OEa), U35.19 (OEb); also elsewhere on the board
unnamed: JP3A1.2 (B), U35.16 (O1a)
unnamed: JP3B1.1 (A), U35.18 (O0a)
unnamed: JPA4.2 (C), U35.14 (O2a)
unnamed: JPB4.2 (C), U35.12 (O3a)
unnamed: R201.2, RP203.2 (R1.2), U16.4 (~RAS), U16.5 (NC), U17.4 (~RAS), U17.5 (NC), U18.4 (~RAS), U18.5 (NC), U19.4 (~RAS), U19.5 (NC), U20.5 (NC), U21.5 (NC), U22.5 (NC), U23.5 (NC)
unnamed: R202.2, RP203.4 (R2.2), U20.4 (~RAS), U21.4 (~RAS), U22.4 (~RAS), U23.4 (~RAS)
unnamed: RP203.6 (R3.2), U18.17 (~CAS), U19.17 (~CAS), U22.17 (~CAS), U23.17 (~CAS)
unnamed: RP203.8 (R4.2), U16.17 (~CAS), U17.17 (~CAS), U20.17 (~CAS), U21.17 (~CAS)
unnamed: RP203.10 (R5.2), U16.3 (~WE), U17.3 (~WE), U18.3 (~WE), U19.3 (~WE), U20.3 (~WE), U21.3 (~WE), U22.3 (~WE), U23.3 (~WE)
unnamed: U32.1 (E), U32.15 (E), U34.11 (LE), U35.5 (O2b)
VCC: C16.1, C17.1, C18.1, C19.1, C20.1, R201.1, R202.1, U16.10 (VCC), U17.10 (VCC), U18.10 (VCC), U19.10 (VCC), U20.10 (VCC), U21.10 (VCC), U22.10 (VCC), U23.10 (VCC); also elsewhere on the board
~BCASL1: JPA4.3 (B), U32.5 (O1); also elsewhere on the board
~BCASU1: JPB4.3 (B), U32.11 (O1); also elsewhere on the board
~BRAS0: JP3B1.2 (B), RP203.1 (R1.1); also elsewhere on the board
~BRAS1: JP3A1.1 (A), RP203.3 (R2.1); also elsewhere on the board
~BWE: RP203.9 (R5.1), U35.3 (O3b); also elsewhere on the board
~CASL: U32.3 (A1), U35.6 (I2a); also elsewhere on the board
~CASU: U32.13 (A1), U35.8 (I3a); also elsewhere on the board
~RAS0: U35.2 (I0a); also elsewhere on the board
~RAS1: U35.4 (I1a); also elsewhere on the board
~WE: U35.17 (I3b); also elsewhere on the board

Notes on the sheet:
SPARE
bdra9 does not pass through RP because it does not get to RAMs. But there's a spare resistor in case.
A600 has a KLUDGE here with a 74LS00. Is it needed here too?
JP3 swaps upper and lower RAM banks
Note: JP4 bypasses U32 for 512K system
Note: U20-23, U23 not loaded for 512K system

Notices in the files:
Raemix500.kicad_pcb:
Licensed under CERN OHL v.1.2
